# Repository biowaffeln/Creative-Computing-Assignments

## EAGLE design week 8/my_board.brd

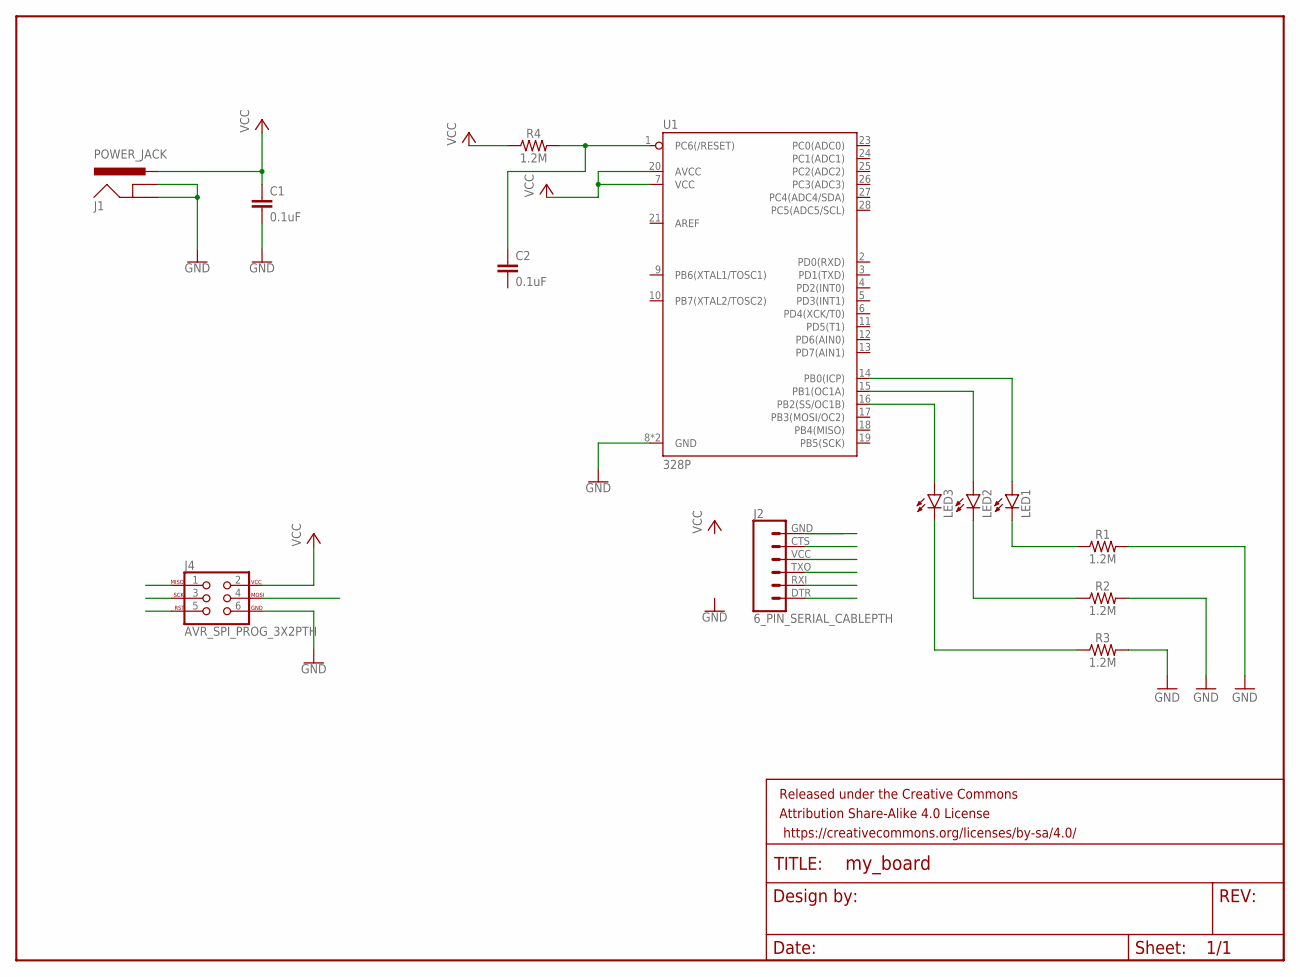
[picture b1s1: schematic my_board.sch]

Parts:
C1, C2: 0.1uF; CAP-PTH-SMALL-KIT
FRAME1: FRAME-LETTER; CREATIVE_COMMONS
J1: POWER_JACK; POWER_JACK_PTH
J2: 6_PIN_SERIAL_CABLEPTH; FTDI_BASIC
J4: AVR_SPI_PROG_3X2PTH; 2X3
LED1, LED2, LED3: LED5MM
R1, R2, R3, R4: 1.2M; 0603
U1: 328P; DIP28

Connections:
GND: C1.2, J1.GND, J1.GNDBREAK, J4.6, R1.2, R2.2, R3.2, U1.8 (GND), U1.22 (GND)
unnamed: LED1.K (C), R1.1
unnamed: LED1.A, U1.14 (PB0(ICP))
unnamed: LED2.K (C), R2.1
unnamed: LED2.A, U1.15 (PB1(OC1A))
unnamed: LED3.K (C), R3.1
unnamed: LED3.A, U1.16 (PB2(SS/OC1B))
unnamed: C2.1, R4.2, U1.1 (PC6(/RESET))
VCC: C1.1, J1.PWR, J4.2, R4.1, U1.7 (VCC), U1.20 (AVCC)

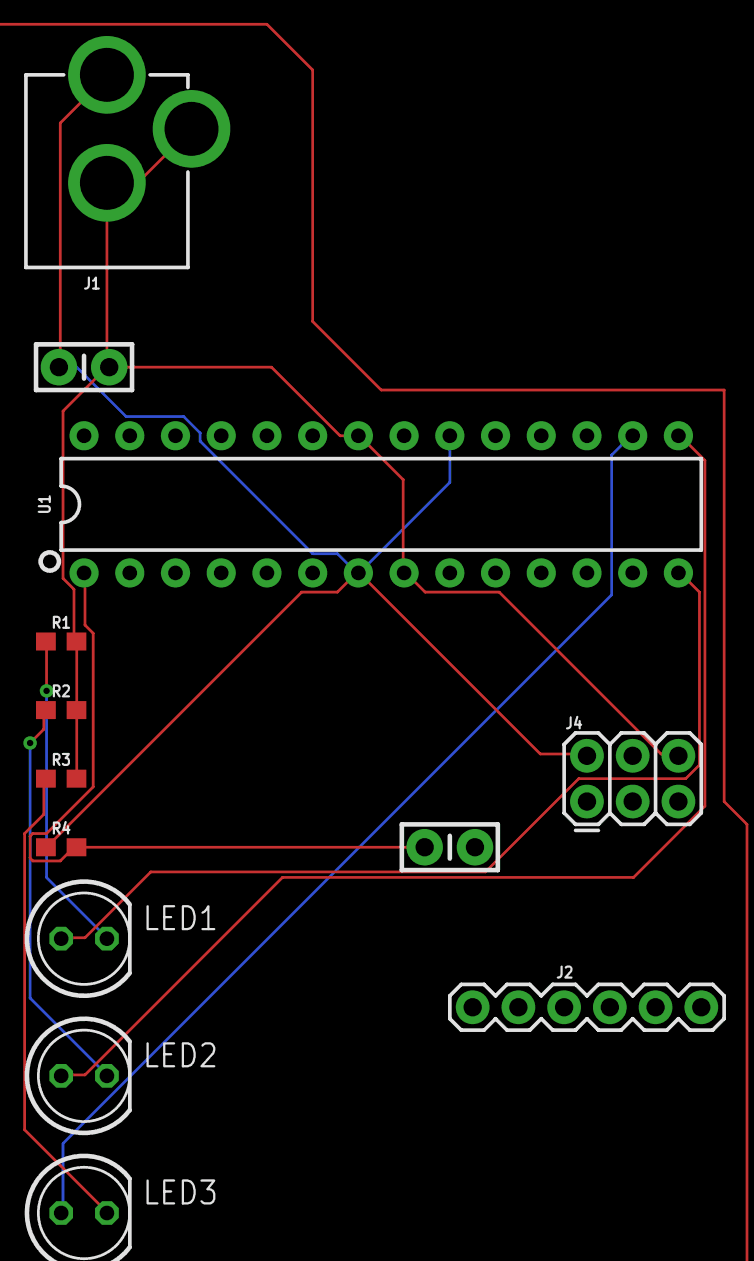
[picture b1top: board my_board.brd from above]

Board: 2 copper layers, 14 parts (0 on the bottom side), 9 nets.

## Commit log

2019-09-30 name ports with define
2019-10-01 generate blink sequences as lists
2019-10-01 implement input logic + fix some reset bugs
2019-10-01 DRYing things up
2019-10-01 comments and formatting
2019-10-06 add documentation
2019-10-07 moved stuff to week 1 folder
2019-10-07 renamed docs to readme
2019-10-13 week 2 documentation
2019-10-17 move gitignore up one folder
2019-10-17 document lab 1 and add code
2019-10-17 change wording for lab 02-04
2019-10-20 week 3 documentation
2019-10-26 add week 4 documentation skeleton
2019-10-26 add processing code
2019-10-27 add images and videos
2019-10-27 add arduino code
2019-10-28 expand on the readme text
2019-11-11 fix week4 and add week6
2019-12-01 add week 8
2019-12-10 update wording
2019-12-10 project log notes

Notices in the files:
parts and their libraries:
SparkFun-Aesthetics: Licensing: Creative Commons ShareAlike 4.0 International - https://creativecommons.org/licenses/by-sa/4.0
SparkFun-Aesthetics: Released under the Creative Commons Attribution Share-Alike 4.0 License
SparkFun-Aesthetics: https://creativecommons.org/licenses/by-sa/4.0
